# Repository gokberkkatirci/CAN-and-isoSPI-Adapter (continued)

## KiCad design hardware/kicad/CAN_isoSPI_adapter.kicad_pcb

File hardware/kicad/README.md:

# KiCad design (Nano R4 adapter)

Open [CAN_isoSPI_adapter.kicad_pro](CAN_isoSPI_adapter.kicad_pro) in **KiCad 10.0.6** or newer. R0E uses a single schematic sheet with four circuit sections, a routed 82 × 64 mm PCB, and project-local symbols, footprints and 3D visualization models.

The board has six diagnostic probe pads. See the [test point map](../../docs/r0b.md#probe-points) and the [R0C](../../docs/r0c.md), [R0D](../../docs/r0d.md) and [R0E](../../docs/r0e.md) changes. Mount H3 with nylon hardware only.

Keep the schematic, PCB, project, custom rules and library tables together. The PCB uses F.Cu for components and short signals, In1.Cu for separate USB and CAN ground zones, In2.Cu for the USB supply zone and routing, and B.Cu for routing. The cable domains are floating and the custom DRC rules preserve their copper separation.

In PCB Editor, choose **View → 3D Viewer**. See [model coverage](models/README.md) for the standard KiCad models, drawing-based models and optional manufacturer STEP files. The Teensy 4.1 adapter in [../teensy41](../teensy41/README.md) reuses these models.

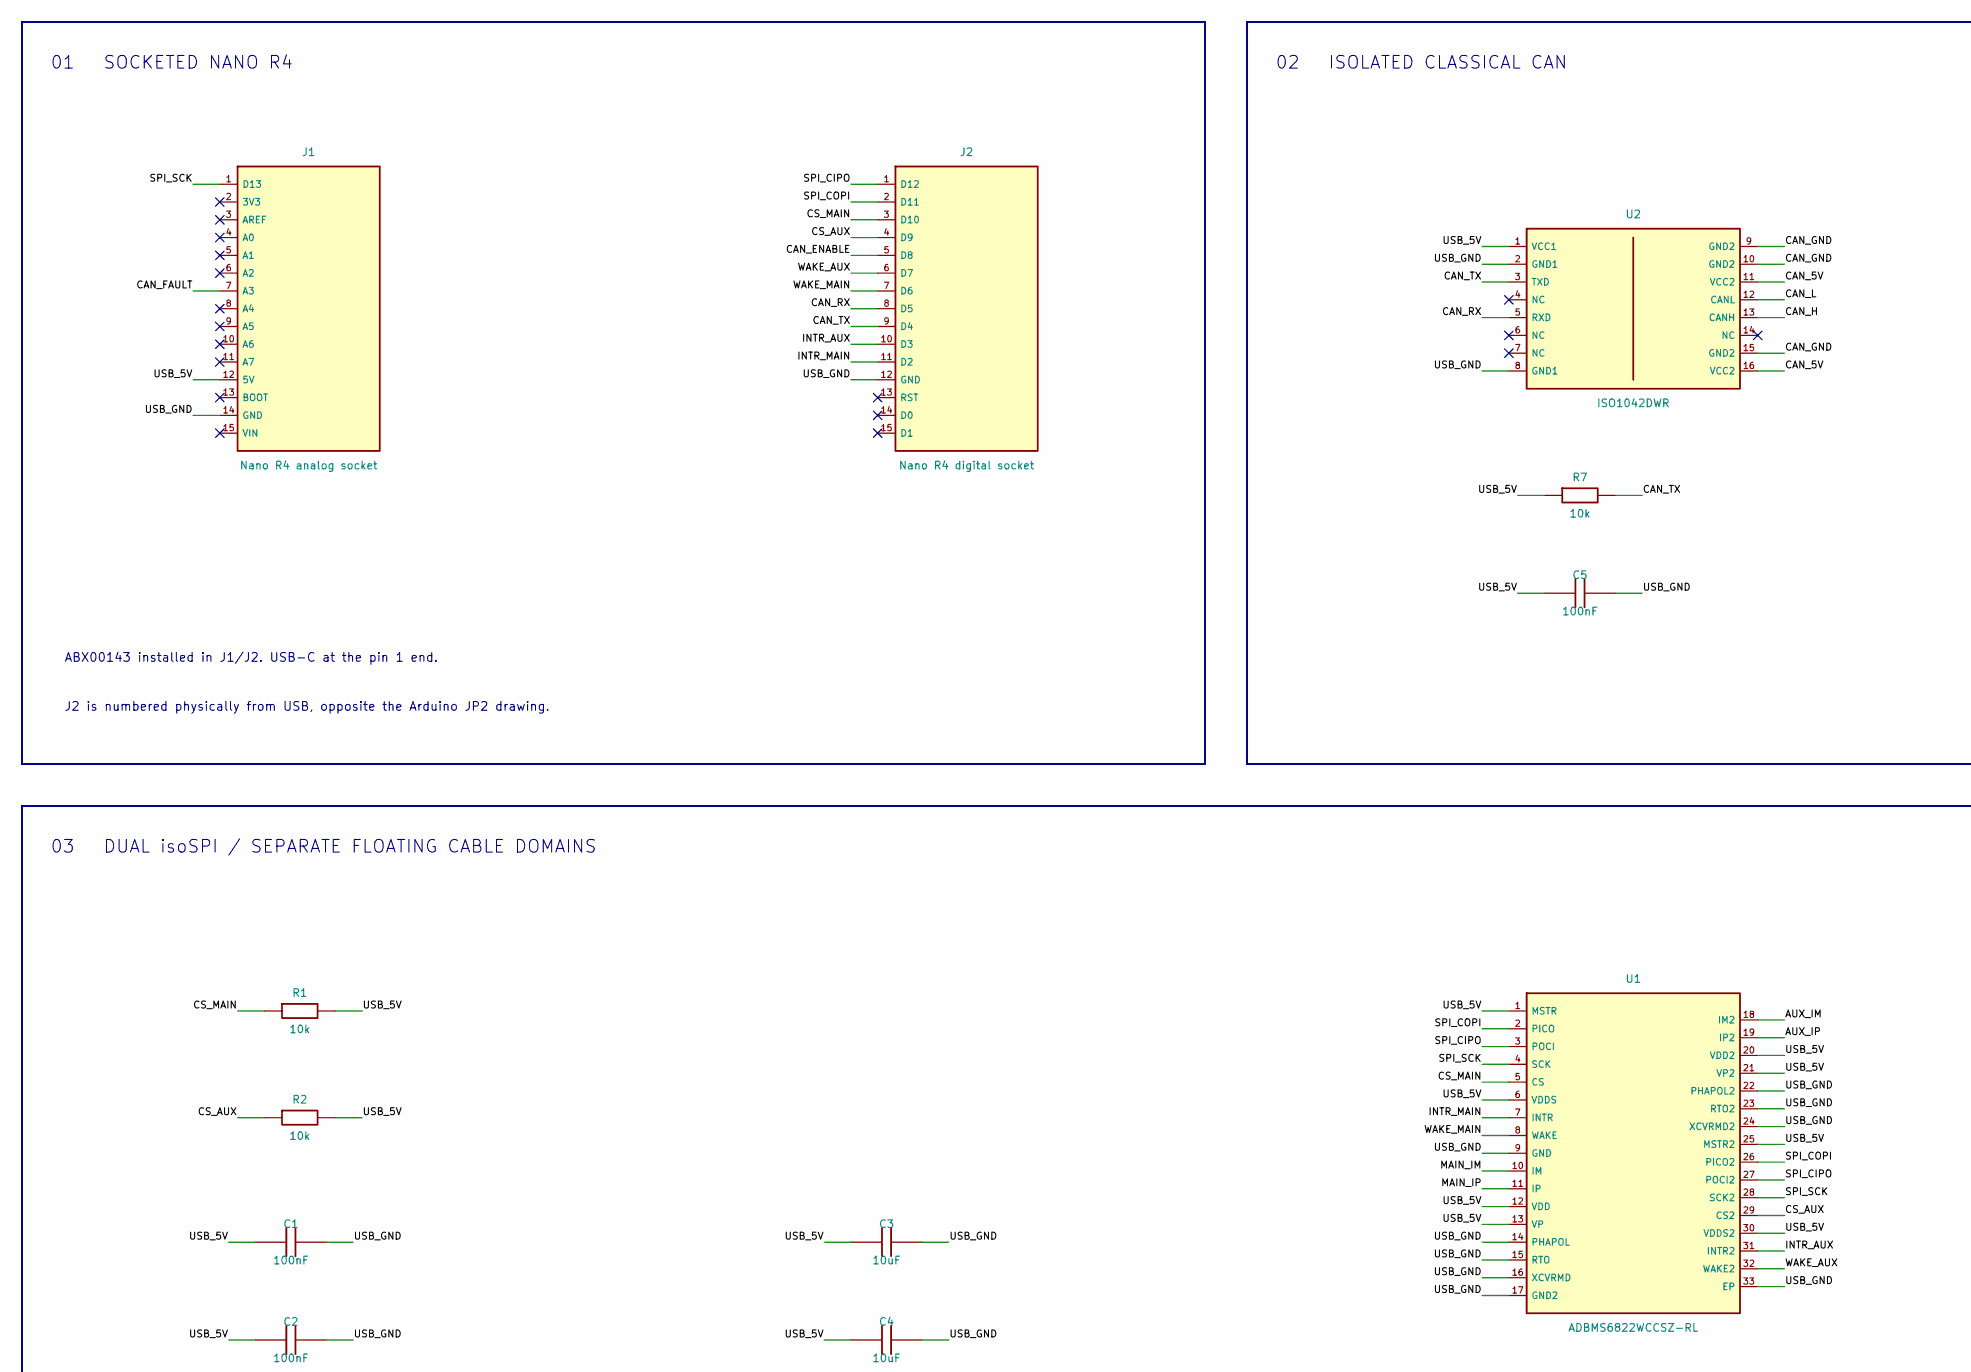
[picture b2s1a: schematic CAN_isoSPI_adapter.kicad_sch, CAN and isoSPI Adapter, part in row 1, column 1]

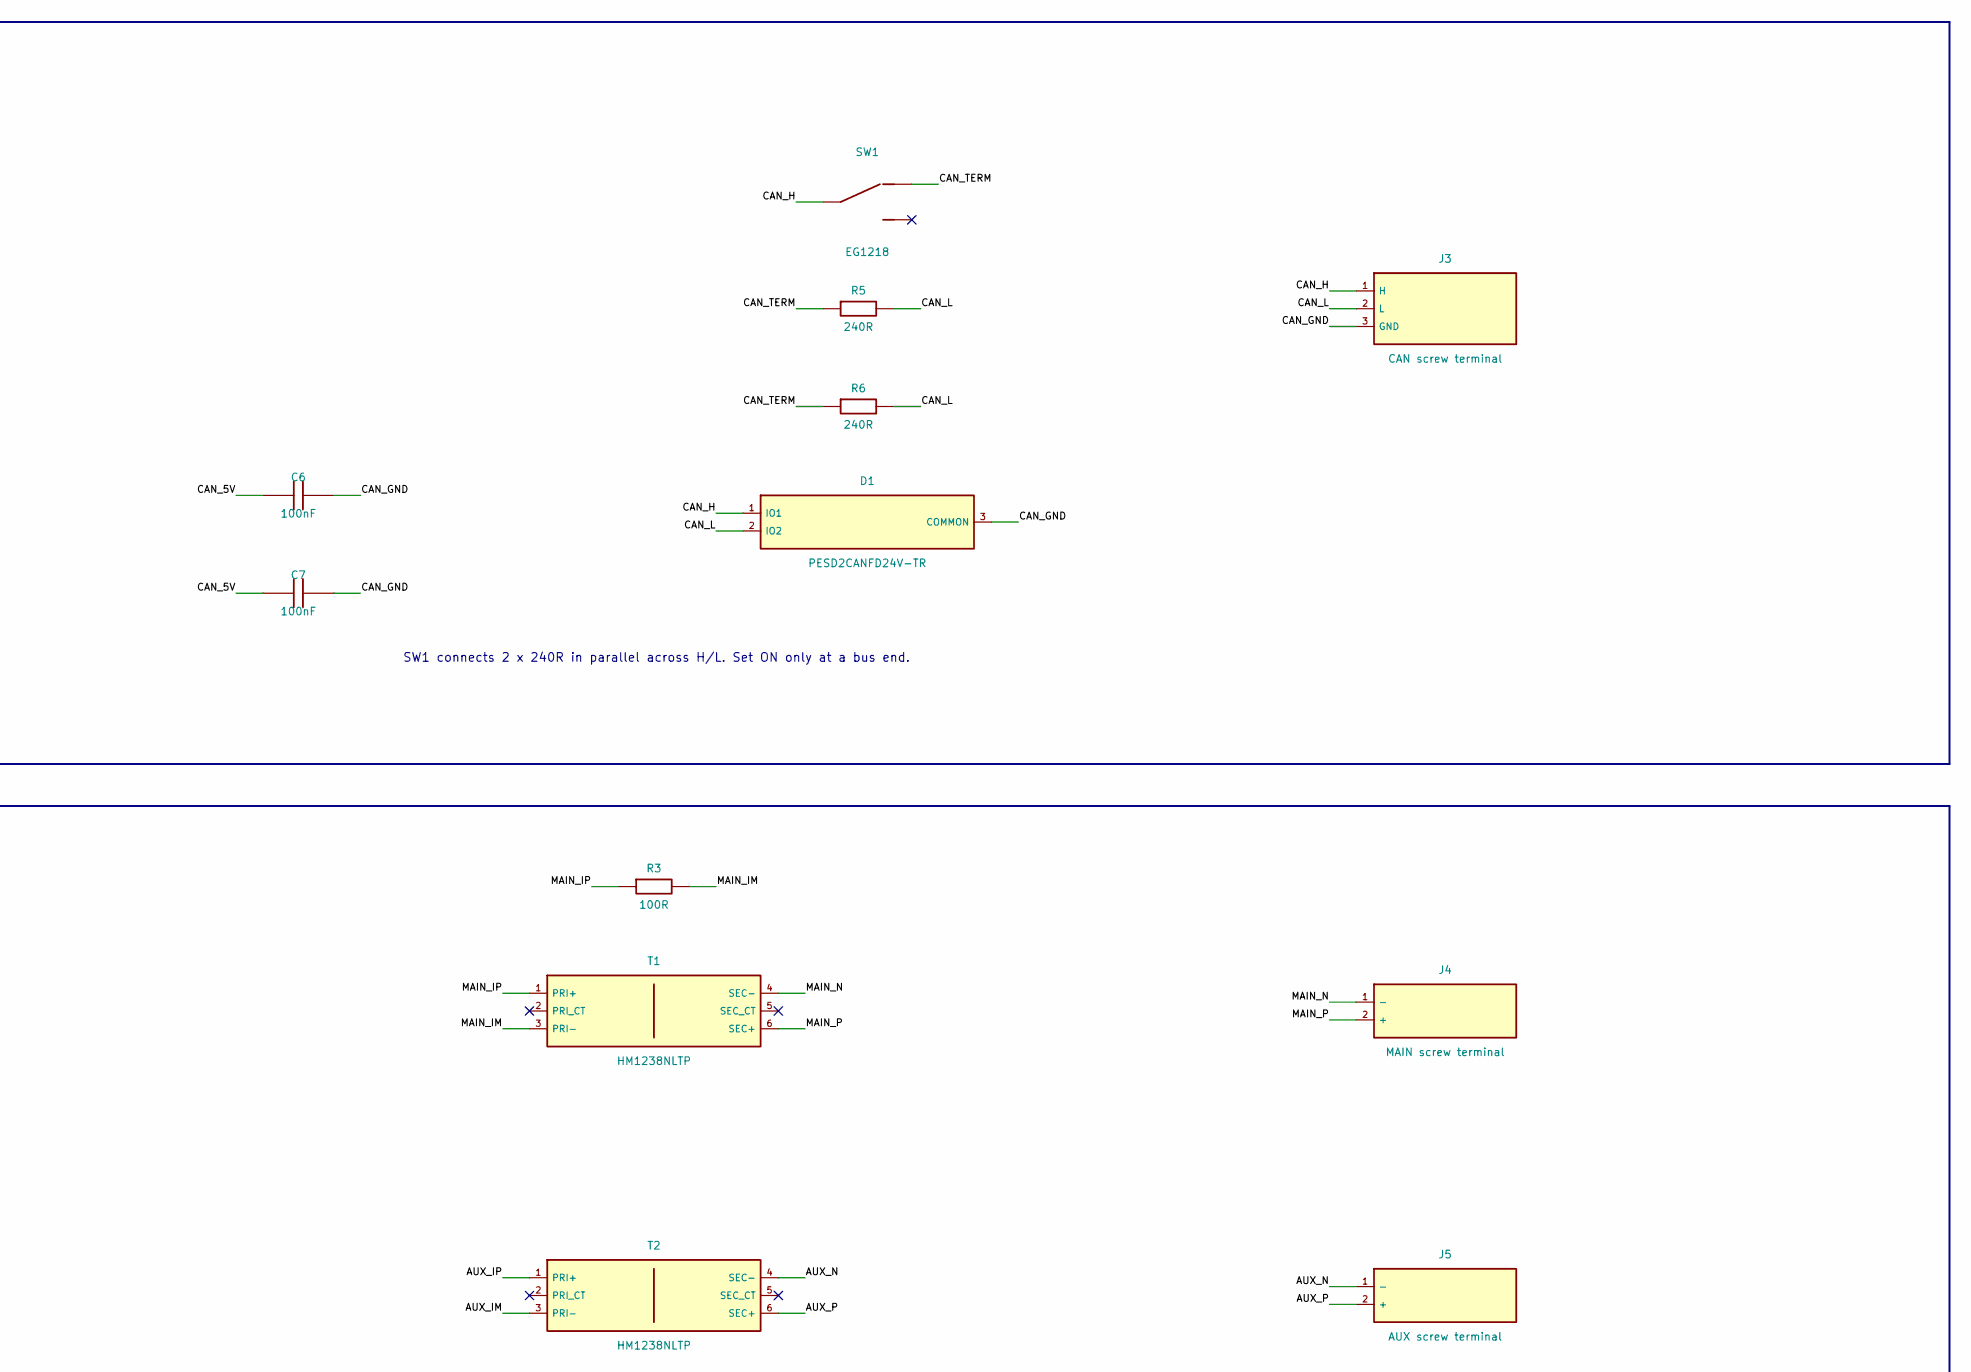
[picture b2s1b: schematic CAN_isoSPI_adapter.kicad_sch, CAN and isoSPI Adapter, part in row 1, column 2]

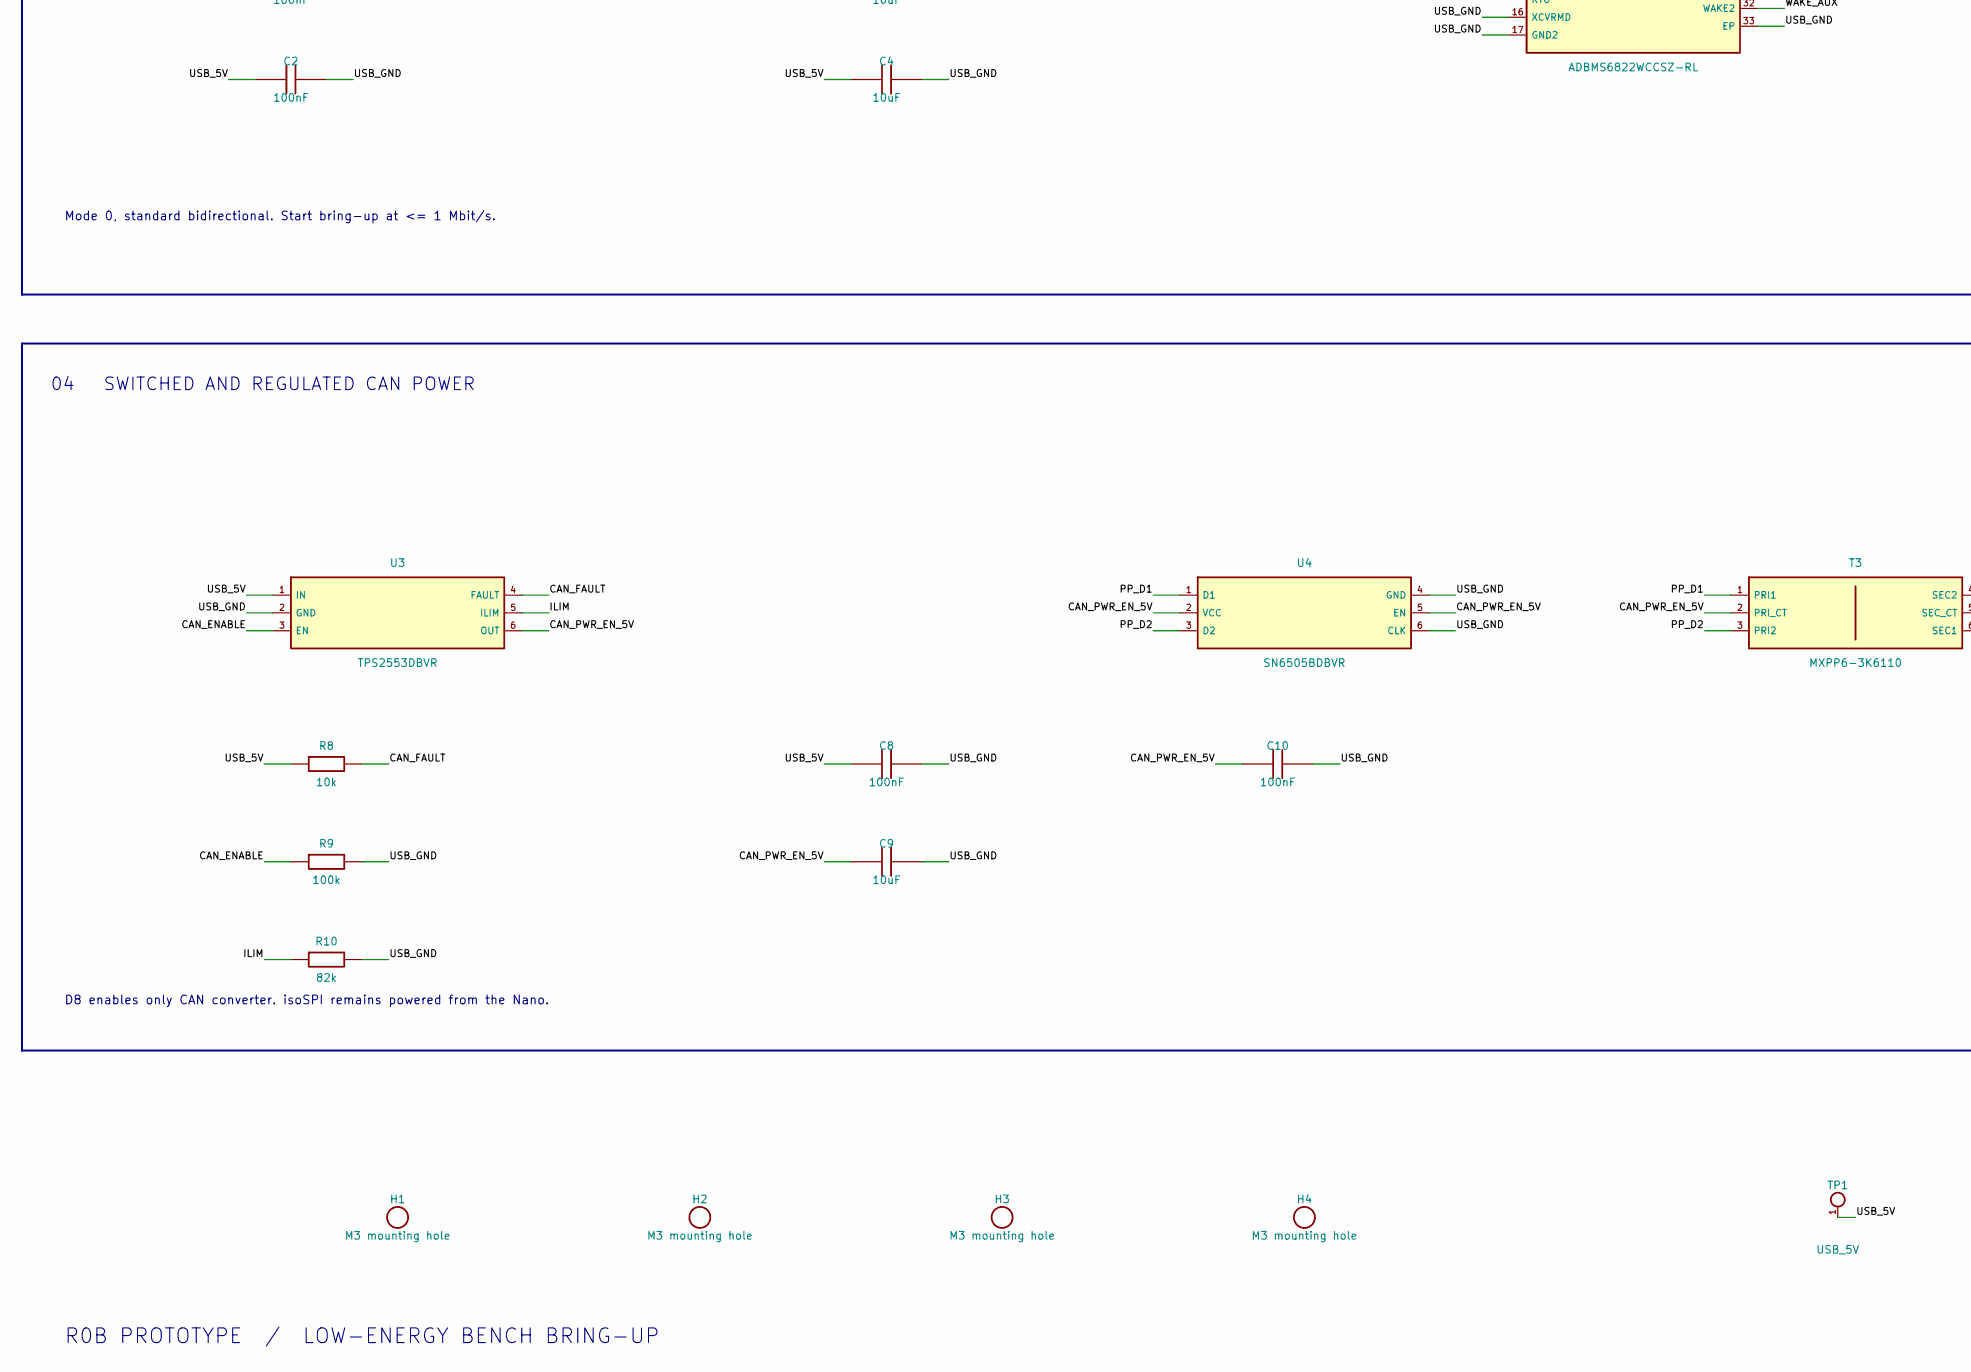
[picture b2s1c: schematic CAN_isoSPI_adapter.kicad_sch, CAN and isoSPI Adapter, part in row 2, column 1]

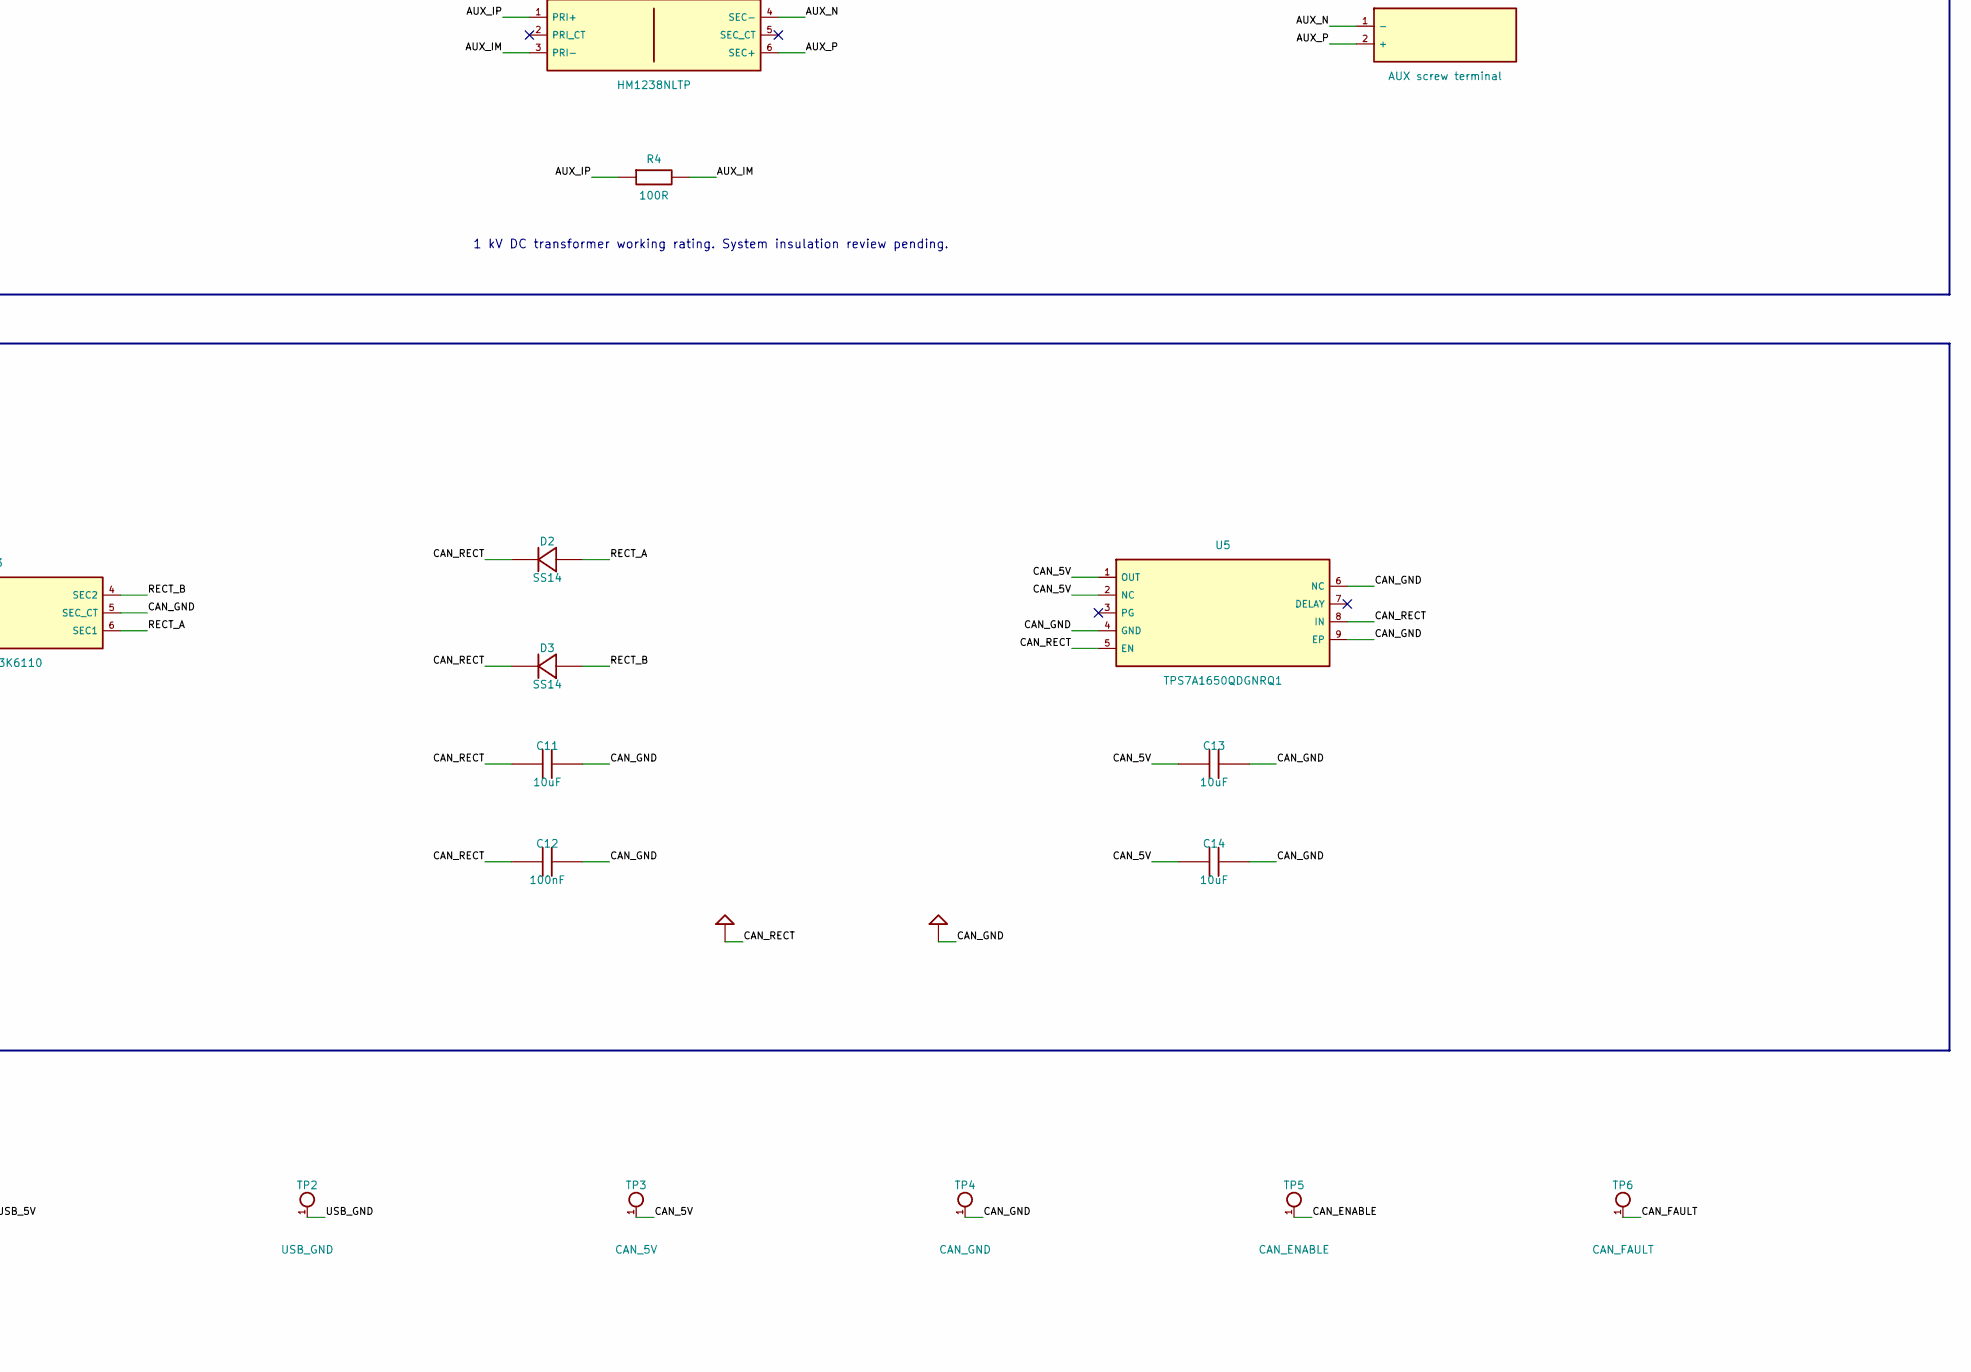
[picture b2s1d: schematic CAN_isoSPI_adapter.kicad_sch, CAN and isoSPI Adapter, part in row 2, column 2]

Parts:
C1, C2, C5, C6, C7, C8, C10, C12: 100nF; C_1206_3216Metric; MPN CL31B104KBCNNNC; JLCPCB Part # C24497
C3, C4, C9, C11, C13, C14: 10uF; C_1206_3216Metric; MPN CL31B106KAHNNNE; JLCPCB Part # C14860
D1: PESD2CANFD24V-TR; SOT-23; MPN PESD2CANFD24V-TR; JLCPCB Part # C552486
D2, D3: SS14; D_SMA; MPN SS14; JLCPCB Part # C2480
H1, H2, H3, H4: M3 mounting hole; MountingHole_3.2mm_M3; MPN Mechanical
J1: Nano R4 analog socket; PinSocket_1x15_P2.54mm_Vertical; MPN SSW-115-01-G-S
J2: Nano R4 digital socket; PinSocket_1x15_P2.54mm_Vertical; MPN SSW-115-01-G-S
J3: CAN screw terminal; TerminalBlock_Phoenix_MKDS-1,5-3-5.08_1x03_P5.08mm_Horizont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; MPN 1715734; JLCPCB Part # C480520
J4: MAIN screw terminal; TerminalBlock_Phoenix_MKDS-1,5-2-5.08_1x02_P5.08mm_Horizont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; MPN 1715721; JLCPCB Part # C480516
J5: AUX screw terminal; TerminalBlock_Phoenix_MKDS-1,5-2-5.08_1x02_P5.08mm_Horizont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; MPN 1715721; JLCPCB Part # C480516
R1, R2, R7, R8: 10k; R_1206_3216Metric; MPN 1206W4F1002T5E; JLCPCB Part # C17902
R3, R4: 100R; R_1206_3216Metric; MPN RC1206FR-07100RL; JLCPCB Part # C137392
R5, R6: 240R; R_1206_3216Metric; MPN 1206W4F2400T5E; JLCPCB Part # C17961
R9: 100k; R_1206_3216Metric; MPN 1206W4F1003T5E; JLCPCB Part # C17900
R10: 82k; R_1206_3216Metric; MPN 1206W4F8202T5E; JLCPCB Part # C17979
SW1: EG1218; MPN EG1218; JLCPCB Part # C273394
T1, T2: HM1238NLTP; MPN HM1238NLTP-CND; JLCPCB Part # C49230397
T3: MXPP6-3K6110; MPN MXPP6-3K6110; JLCPCB Part # C19943838
TP1: USB_5V; TestPoint_Pad_D1.5mm; MPN USB_5V
TP2: USB_GND; TestPoint_Pad_D1.5mm; MPN USB_GND
TP3: CAN_5V; TestPoint_Pad_D1.5mm; MPN CAN_5V
TP4: CAN_GND; TestPoint_Pad_D1.5mm; MPN CAN_GND
TP5: CAN_ENABLE; TestPoint_Pad_D1.5mm; MPN CAN_ENABLE
TP6: CAN_FAULT; TestPoint_Pad_D1.5mm; MPN CAN_FAULT
U1: ADBMS6822WCCSZ-RL; ADBMS6822_05-08-7057; MPN ADBMS6822WCCSZ-RL; JLCPCB Part # C19190031
U2: ISO1042DWR; SOIC-16W_7.5x10.3mm_P1.27mm; MPN ISO1042DWR; JLCPCB Part # C1848126
U3: TPS2553DBVR; SOT-23-6; MPN TPS2553DBVR; JLCPCB Part # C55266
U4: SN6505BDBVR; SOT-23-6; MPN SN6505BDBVR; JLCPCB Part # C74518
U5: TPS7A1650QDGNRQ1; MSOP-8-1EP_3x3mm_P0.65mm_EP1.73x1.85mm; MPN TPS7A1650QDGNRQ1; JLCPCB Part # C2832237

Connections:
/AUX_IM: R4.2, T2.3 (PRI-), U1.18 (IM2)
/AUX_IP: R4.1, T2.1 (PRI+), U1.19 (IP2)
/AUX_N: J5.1 (-), T2.4 (SEC-)
/AUX_P: J5.2 (+), T2.6 (SEC+)
/CAN_5V: C6.1, C7.1, C13.1, C14.1, TP3.1, U2.11 (VCC2), U2.16 (VCC2), U5.1 (OUT), U5.2 (NC)
/CAN_ENABLE: J2.5 (D8), R9.1, TP5.1, U3.3 (EN)
/CAN_FAULT: J1.7 (A3), R8.2, TP6.1, U3.4 (FAULT)
/CAN_GND: C6.2, C7.2, C11.2, C12.2, C13.2, C14.2, D1.3 (COMMON), J3.3 (GND), T3.5 (SEC_CT), TP4.1, U2.9 (GND2), U2.10 (GND2), U2.15 (GND2), U5.4 (GND), U5.6 (NC), U5.9 (EP)
/CAN_H: D1.1 (IO1), J3.1 (H), SW1.2 (COM), U2.13 (CANH)
/CAN_L: D1.2 (IO2), J3.2 (L), R5.2, R6.2, U2.12 (CANL)
/CAN_PWR_EN_5V: C9.1, C10.1, T3.2 (PRI_CT), U3.6 (OUT), U4.2 (VCC), U4.5 (EN)
/CAN_RECT: C11.1, C12.1, D2.1 (K), D3.1 (K), U5.5 (EN), U5.8 (IN)
/CAN_RX: J2.8 (D5), U2.5 (RXD)
/CAN_TERM: R5.1, R6.1, SW1.1 (ON)
/CAN_TX: J2.9 (D4), R7.2, U2.3 (TXD)
/CS_AUX: J2.4 (D9), R2.1, U1.29 (CS2)
/CS_MAIN: J2.3 (D10), R1.1, U1.5 (CS)
/ILIM: R10.1, U3.5 (ILIM)
/INTR_AUX: J2.10 (D3), U1.31 (INTR2)
/INTR_MAIN: J2.11 (D2), U1.7 (INTR)
/MAIN_IM: R3.2, T1.3 (PRI-), U1.10 (IM)
/MAIN_IP: R3.1, T1.1 (PRI+), U1.11 (IP)
/MAIN_N: J4.1 (-), T1.4 (SEC-)
/MAIN_P: J4.2 (+), T1.6 (SEC+)
/PP_D1: T3.1 (PRI1), U4.1 (D1)
/PP_D2: T3.3 (PRI2), U4.3 (D2)
/RECT_A: D2.2 (A), T3.6 (SEC1)
/RECT_B: D3.2 (A), T3.4 (SEC2)
/SPI_CIPO: J2.1 (D12), U1.3 (POCI), U1.27 (POCI2)
/SPI_COPI: J2.2 (D11), U1.2 (PICO), U1.26 (PICO2)
/SPI_SCK: J1.1 (D13), U1.4 (SCK), U1.28 (SCK2)
/USB_5V: C1.1, C2.1, C3.1, C4.1, C5.1, C8.1, J1.12 (5V), R1.2, R2.2, R7.1, R8.1, TP1.1, U1.1 (MSTR), U1.6 (VDDS), U1.12 (VDD), U1.13 (VP), U1.20 (VDD2), U1.21 (VP2), U1.25 (MSTR2), U1.30 (VDDS2), U2.1 (VCC1), U3.1 (IN)
/USB_GND: C1.2, C2.2, C3.2, C4.2, C5.2, C8.2, C9.2, C10.2, J1.14 (GND), J2.12 (GND), R9.2, R10.2, TP2.1, U1.9 (GND), U1.14 (PHAPOL), U1.15 (RTO), U1.16 (XCVRMD), U1.17 (GND2), U1.22 (PHAPOL2), U1.23 (RTO2), U1.24 (XCVRMD2), U1.33 (EP), U2.2 (GND1), U2.8 (GND1), U3.2 (GND), U4.4 (GND), U4.6 (CLK)
/WAKE_AUX: J2.6 (D7), U1.32 (WAKE2)
/WAKE_MAIN: J2.7 (D6), U1.8 (WAKE)

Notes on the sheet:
01 SOCKETED NANO R4
02 ISOLATED CLASSICAL CAN
03 DUAL isoSPI / SEPARATE FLOATING CABLE DOMAINS
04 SWITCHED AND REGULATED CAN POWER
ABX00143 installed in J1/J2. USB-C at the pin 1 end.
J2 is numbered physically from USB, opposite the Arduino JP2 drawing.
SW1 connects 2 x 240R in parallel across H/L. Set ON only at a bus end.
Mode 0, standard bidirectional. Start bring-up at <= 1 Mbit/s.
1 kV DC transformer working rating. System insulation review pending.
D8 enables only CAN converter. isoSPI remains powered from the Nano.
R0B PROTOTYPE / LOW-ENERGY BENCH BRING-UP

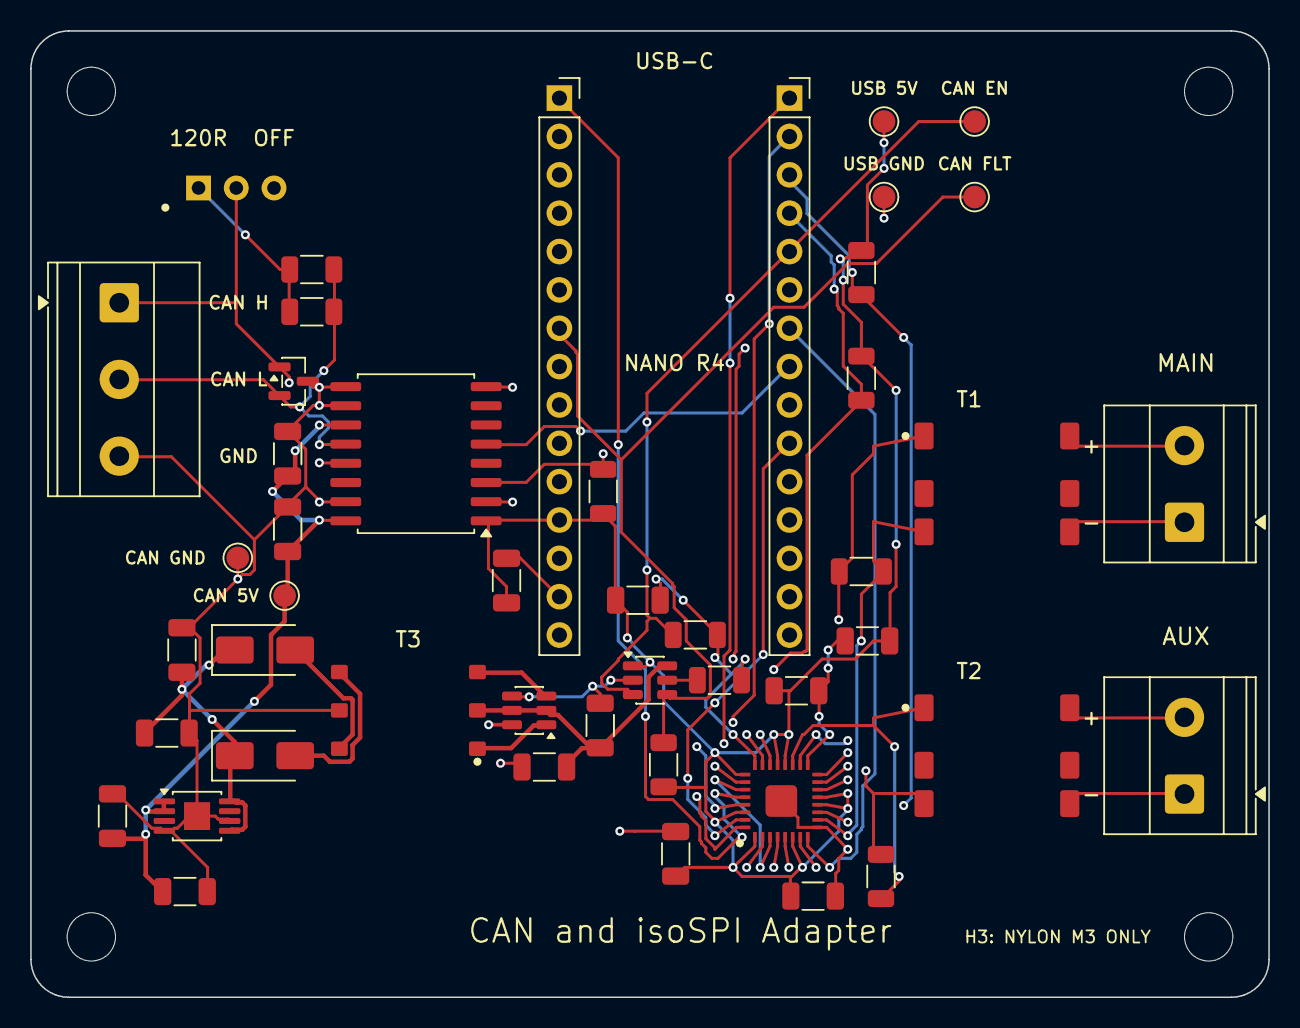
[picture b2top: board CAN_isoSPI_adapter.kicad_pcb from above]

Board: 4 copper layers, 82.0 x 64.0 mm, 51 parts (0 on the bottom side), 35 nets.

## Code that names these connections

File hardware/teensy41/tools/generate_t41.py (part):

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        "Teensy 4.1 sits in J2/J3 (8.5 mm sockets). Keep the VIN-VUSB pads joined: VUSB powers the USB PHY. Never plug the Teensy micro-USB.",
        "J4/J5 pogo pins reach the Teensy USB device D-/D+ pads under the module; the carrier USB-C carries data and power.",
        "CAN1-3 use Teensy FlexCAN1-3; CAN4-6 use MCP2518FD on SPI1. Each CAN port has its own isolated supply and ground.",
        "DSUB-9 female, CiA 303-1 / PEAK pinout: 2 CAN_L, 7 CAN_H, 3 and 6 CAN_GND, 5 and shell to shield RC.",
        "isoSPI ports use CND-tek HM1238NLTP (1000 V DC working, basic insulation). Keep 8 mm copper clearance per port.",
    ]
    for i, t in enumerate(notes):
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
